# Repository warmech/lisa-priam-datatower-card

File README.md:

# Priam DataTower Interface Card for the Apple Lisa Expansion Bus
 
## Thoughts

If we're going to compile the LOS source code, we're going to need a Priam DataTower. [Said Al Kossow in regard to compiling LOS](https://forum.vcfed.org/index.php?threads/wtb-working-apple-lisa.1246678/page-2):

>you really need something like a Priam Datatower (ie more disk space) to build LOS
>
>the tools are all there in the Version 3 Pascal Workshop.

It seems the compilation process is just too demanding of storage capacity; the 80MB of space the DataTower offered in 1982/3 would have certainly been more than enough (and had a price tag that reflected such a wealth of space).

The driver for the Priam DataTower is baked into LOS and, from the sound of it, no additional software is needed to mount DataTower volumes. Additionally, in the 09/1984 issue of Signal 16, the writers had the following to say regarding the DataTower:

>Signal 16, September 1984
>Priam's DataTower Arrives
>
>Not long after our Signal #13 story about Priam Whamos was published, we got a call from Bill North at Priam, who asked if we would like to find out more about their 86MB disk for the Lisa. The unit is called a DataTower, features a built-in 1/4" tape drive for backup, and is being retailed to the Lisa market as the MassFile by Tecmar. Negotiations began, and phone calls and letters started to wander back and forth between Priam and Semaphore.
>
>Last week, three boxes totaling 110 pounds arrived from San Jose. It was the DataTower. We hate to open a delivery until we're ready to write about it (or at least take good notes), otherwise we might forget some of those interesting first impressions. And, while this copy of Signal was still going through rework at the time (and could easily handle a few last minute changes), we couldn't possibly finish a comprehensive review of the DataTower and include it in the issue. So there was obviously no reason to open the shipment just yet. On the other hand, not opening a newly arrived product is like putting off opening Christmas packages even though it's December 25th. It didn't take long before we reached a compromise: we'd open the shipment, spend just half a day or so checking it out, report on just that much, and then do the rest of the investigation (or at least enough to look like we're making progress) when the next issue rolls around.
>
>We opened the first of the two small boxes and found a blank 1/4" tape cartridge, a power cord, a head cleaning kit, and a photocopy of a 180-page preliminary product specification (slightly too thick for its single staple). The second small box held another blank cartridge, an interface card designed to plug into a Lisa, and a cable to connect the card to the DataTower. The third box held the DataTower itself, contained in a 7" wide, 26" tall and 20" deep metal cabinet that's just right for standing alongside a desk. Unpacking dropped the unit's weight down to about 80 pounds.
>
>It only took us about ten minutes to install everything. The product specification that was included is really engineering documentation designed for programmer types who need to worry about interfacing and writing drivers and all of those esoteric subjects. It doesn't really try to be end user documentation describing how to simply make the unit operate with a Lisa. So we just got out our old Apple documentation on installing a Lisa two-port card, followed all the pictures and went through all the installation steps (but with the Priam card), attached the cable, and powered everything on.
>
>The Lisa we used was an original model that was upgraded to a 2/5, but which still has old ROMs so that the Startup Menu shows two twiggy slots. With the Priam's interface card installed, we were expecting to now find another printed circuit board icon in the Startup Menu. Instead, the menu included an actual little DataTower icon! Those ROMs aren't so old, after all...
>
>We quickly installed a 3.0 Office System on the new disk, and we were off and running. Now Attributes shows 142,420 blocks for our disk device.
>
>One way to think of the DataTower is as something like another Profile, except that it's a lot bigger and faster. Unfortunately, it's noisier too, just enough noisier to be a bit too loud for a nice, calm office environment. Naturally, it's also more expensive. At $8,995 suggested retail, the cost per megabyte is a lot less than on a Profile (and you get the built-in tape drive, too).
>
>Backing up the DataTower is a lot simpler than backing up a Profile, at least in the sense of not requiring a couple of boxes of floppies and lots of operator attention. By duplicating the disk icon, you can start copying the disk to the cartridge tape. So far, we've tried this once and soon realized that 3.0 copies the entire disk image to tape, regardless of how many files are actually stored on the disk, so we canceled the operation once it asked us to insert tape cartridge number two. We'll try a complete save again when we have a bit more time, and let you know how it goes.
>
>We've also started work on an interesting little project that will try to fully exercise the DataTower in a special way. Stay tuned for more details.

This would seem to indicate that the Lisa is capable of booting from a DataTower and that such a boot option will show up at the main boot menu.

The SMART-T protocol documentation is located in the src\priam-src-data directory; this will need to be cross-referenced with the Lisa source code in order to determine next steps for an emulator.

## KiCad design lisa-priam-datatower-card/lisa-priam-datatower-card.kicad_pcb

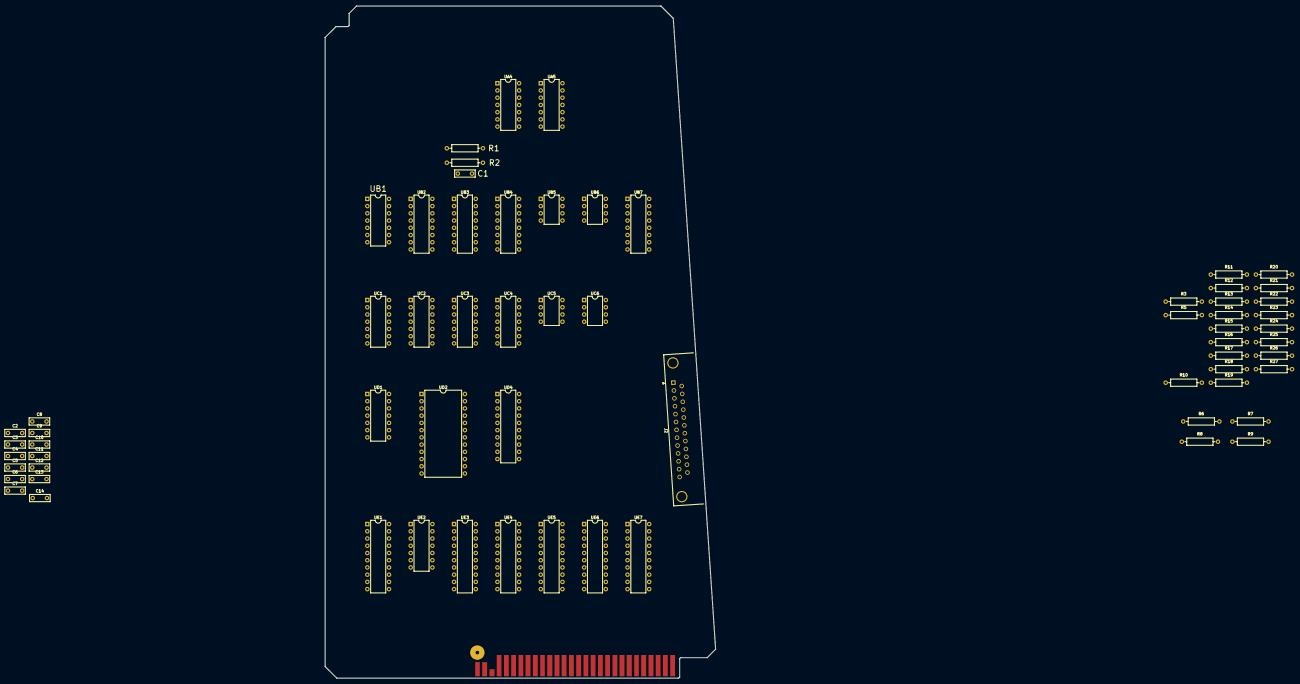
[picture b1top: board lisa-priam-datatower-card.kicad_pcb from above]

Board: 2 copper layers, 137.2 x 236.2 mm, 67 parts (0 on the bottom side), 119 nets, no tracks yet.

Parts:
C1, C2, C3, C4, C5, C6, C7, C8, C9, C10, C11, C12, C13, C14: 0.1uF 50V; C_Disc_D7.0mm_W2.3mm_P5.00mm
J1: Lisa Expansion Card Edge; Apple_Lisa_ExpansionBus_CardEdge
J2: DB25_Receptacle_MountingHoles; DSUB-25_Female_Horizontal_P2.77x2.84mm_EdgePinOffset4.94mm_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
R1, R2, R3, R5: 3.3K; R_Axial_DIN0309_L9.0mm_D2.54mm_P12.70mm_Horizontal
R6, R10, R12, R14, R16, R22, R24, R26: 390; R_Axial_DIN0309_L9.0mm_D2.54mm_P12.70mm_Horizontal
R7, R8, R11, R13, R15, R17, R18, R20, R23, R25, R27: 330; R_Axial_DIN0309_L9.0mm_D2.54mm_P12.70mm_Horizontal
R9, R19, R21: 220; R_Axial_DIN0309_L9.0mm_D2.54mm_P12.70mm_Horizontal
UA4: 74LS164; DIP-14_W7.62mm
UA5: 74LS02; DIP-14_W7.62mm
UB1: 74LS02; DIP-14_W7.62mm
UB2, UB3, UB4, UB7: 74LS112; DIP-16_W7.62mm
UB5, UB6: 75463; DIP-8_W7.62mm
UC1: 74LS125; DIP-14_W7.62mm
UC2: 74LS32; DIP-14_W7.62mm
UC3: 74LS132; DIP-14_W7.62mm
UC4: 74LS00; DIP-14_W7.62mm
UC5, UC6: 75463; DIP-8_W7.62mm
UD1: 74LS00; DIP-14_W7.62mm
UD2: 2716; DIP-24_W15.24mm
UD4: 8304; DIP-20_W7.62mm
UE1, UE4, UE5, UE6, UE7: 74LS374; DIP-20_W7.62mm
UE2: 74LS280; DIP-14_W7.62mm
UE3: 74LS244; DIP-20_W7.62mm

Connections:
+5V: C1.2, C2.2, C3.2, C4.2, C5.2, C6.2, C7.2, C8.2, C9.2, C10.2, C11.2, C12.2, C13.2, C14.2, J1.55 (+5V), J1.56 (+5V), R1.1, R2.1, R3.2, R5.1, R7.2, R9.1, R11.2, R13.2, R15.2, R17.2, R19.2, R21.1, R23.2, R25.2, R27.2, UA4.14 (VCC), UA5.14 (VCC), UB1.14 (VCC), UB2.16 (VCC), UB3.16 (VCC), UB4.16 (VCC), UB5.8 (VCC), UB6.8 (VCC), UB7.16 (VCC), UC1.14 (VCC), UC2.14 (VCC), UC3.14 (VCC), UC4.14 (VCC), UC5.8 (VCC), UC6.8 (VCC), UD1.14 (VCC), UD2.21 (VPP), UD2.24 (VCC), UD4.20 (VCC), UE1.20 (VCC), UE2.14 (VCC), UE3.20 (VCC), UE4.20 (VCC), UE5.20 (VCC), UE6.20 (VCC), UE7.20 (VCC)
/BA1: J1.31 (BA1), UD2.8 (A0), UE1.3 (D0)
/BA2: J1.32 (BA2), UD2.7 (A1), UE1.4 (D1)
/BA3: J1.33 (BA3), UD2.6 (A2), UE1.7 (D2)
/BA4: J1.34 (BA4), UD2.5 (A3), UE1.8 (D3)
/BA5: J1.35 (BA5), UD2.4 (A4), UE1.13 (D4)
/BA7: J1.37 (BA7), UD2.2 (A6), UE1.17 (D6)
/BA8: J1.38 (BA8), UD2.1 (A7), UE1.18 (D7)
/BAA: J1.40 (BA10), UD2.22 (A9)
/BAB: J1.41 (BA11), UD2.19 (A10)
/BD0: J1.30 (BD0), UE3.18 (O0a), UE4.3 (D0), UE5.2 (O0)
/BD1: J1.29 (BD1), UE3.16 (O1a), UE4.4 (D1), UE5.5 (O1)
/BD2: J1.28 (BD2), UE3.14 (O2a), UE4.7 (D2), UE5.6 (O2)
/BD3: J1.27 (BD3), UE3.12 (O3a), UE4.8 (D3), UE5.9 (O3)
/BD4: J1.26 (BD4), UE3.9 (O0b), UE4.13 (D4), UE5.12 (O4)
/BD5: J1.25 (BD5), UE3.7 (O1b), UE4.14 (D5), UE5.15 (O5)
/BD6: J1.24 (BD6), UE3.5 (O2b), UE4.17 (D6), UE5.16 (O6)
/BD7: J1.23 (BD7), UE3.3 (O3b), UE4.18 (D7), UE5.19 (O7)
/BD8: J1.22 (BD8), UE6.3 (D0), UE7.2 (O0)
/BD9: J1.21 (BD9), UE6.4 (D1), UE7.5 (O1)
/BDA: J1.20 (BD10), UE6.7 (D2), UE7.6 (O2)
/BDB: J1.19 (BD11), UE6.8 (D3), UE7.9 (O3)
/BDC: J1.18 (BD12), UE6.13 (D4), UE7.12 (O4)
/BDD: J1.17 (BD13), UE6.14 (D5), UE7.15 (O5)
/BDE: J1.16 (BD14), UE6.17 (D6), UE7.16 (O6)
/BDF: J1.15 (BD15), UC1.3, UE6.18 (D7), UE7.19 (O7)
/LD0: UD4.1 (A0), UE2.8 (A), UE4.2 (O0), UE5.3 (D0), UE6.2 (O0), UE7.3 (D0)
/LD1: UD4.2 (A1), UE2.9 (B), UE4.5 (O1), UE5.4 (D1), UE6.5 (O1), UE7.4 (D1)
/LD2: UD4.3 (A2), UE2.10 (C), UE4.6 (O2), UE5.7 (D2), UE6.6 (O2), UE7.7 (D2)
/LD3: UD4.4 (A3), UE2.11 (D), UE4.9 (O3), UE5.8 (D3), UE6.9 (O3), UE7.8 (D3)
/LD4: UD4.5 (A4), UE2.12 (E), UE4.12 (O4), UE5.13 (D4), UE6.12 (O4), UE7.13 (D4)
/LD5: UD4.6 (A5), UE2.13 (F), UE4.15 (O5), UE5.14 (D5), UE6.15 (O5), UE7.14 (D5)
/LD6: UD4.7 (A6), UE2.1 (G), UE4.16 (O6), UE5.17 (D6), UE6.16 (O6), UE7.17 (D6)
/LD7: UD4.8 (A7), UE2.2 (H), UE4.19 (O7), UE5.18 (D7), UE6.19 (O7), UE7.18 (D7)
BA6: J1.36 (BA6), UB1.5, UB1.6, UD2.3 (A5), UE1.14 (D5)
BA9: J1.39 (BA9), UC2.12, UD2.23 (A8)
CKH: UC4.8, UE7.11 (Cp)
CKL: UC4.11, UE5.11 (Cp)
CKP: UB3.5 (Q), UB4.1 (C), UC4.10, UC4.12
CPUCK: J1.8 (CPUCK), UB3.13 (C), UB7.1 (C), UB7.13 (C)
GND: C1.1, C2.1, C3.1, C4.1, C5.1, C6.1, C7.1, C8.1, C9.1, C10.1, C11.1, C12.1, C13.1, C14.1, J1.53 (GND), J1.54 (GND), J2.0 (PAD), J2.1, J2.2, J2.4, J2.9, J2.20, J2.24, R6.1, R8.2, R10.1, R12.1, R14.1, R16.1, R18.2, R20.2, R22.1, R24.1, R26.1, UA4.7 (GND), UA5.7 (GND), UB1.7 (GND), UB2.8 (GND), UB3.8 (GND), UB4.2 (K), UB4.8 (GND), UB4.11 (J), UB5.4 (GND), UB6.4 (GND), UB7.8 (GND), UC1.5, UC1.7 (GND), UC2.7 (GND), UC3.7 (GND), UC4.7 (GND), UC5.4 (GND), UC6.4 (GND), UD1.7 (GND), UD2.12 (GND), UD2.18 (/CE), UD2.20 (/OE), UD4.10 (GND), UE1.1 (OE), UE1.10 (GND), UE2.7 (GND), UE3.10 (GND), UE4.10 (GND), UE5.10 (GND), UE6.10 (GND), UE7.10 (GND)
HAD0: J2.16, UB5.5
HAD1: J2.17, UB5.3
HAD2: J2.19, UB6.5
HCBUS0: J2.5, R6.2, R7.1, UD4.19 (B0)
HCBUS1: J2.6, R10.2, R11.1, UD4.18 (B1)
HCBUS2: J2.8, R12.2, R13.1, UD4.17 (B2)
HCBUS3: J2.22, R14.2, R15.1, UD4.16 (B3)
HCBUS4: J2.23, R16.2, R17.1, UD4.15 (B4)
HCBUS5: J2.11, R22.2, R23.1, UD4.14 (B5)
HCBUS6: J2.12, R24.2, R25.1, UD4.13 (B6)
HCBUS7: J2.13, R26.2, R27.1, UD4.12 (B7)
HCBUSP: J2.18, R8.1, R9.2, UC3.1, UC5.3
HUNK: J2.14, UB6.3
LA1: UB5.6, UE1.2 (O0)
LA2: UB5.2, UE1.5 (O1)
LA3: UB6.6, UE1.6 (O2)
LA4: UB6.2, UE1.9 (O3)
LA5: UB4.15 (~R), UE1.12 (O4)
LA7: UD1.13, UE1.16 (O6)
LA8: UC3.9, UE1.19 (O7)
unnamed: J1.13 (/BGINn), J1.14 (/BGOUTn)
unnamed: J1.6 (/IAKn), J1.44 (/VPA)
unnamed: UA4.1 (A), UA4.2 (B), UB2.5 (Q), UC4.1, UC4.9
unnamed: UA4.8 (CLK), UB2.1 (C), UB2.13 (C), UB4.13 (C), UB7.9 (Q)
unnamed: UA4.4 (Qb), UA5.2, UB2.11 (J)
unnamed: UA4.5 (Qc), UA5.3
unnamed: UB1.1, UC1.9
unnamed: UB1.3, UB1.4
unnamed: UA5.1, UB2.3 (J)
unnamed: UB2.6 (~Q), UD1.10
unnamed: UB1.2, UB2.9 (Q), UB4.12 (K), UC4.5, UC4.13, UD1.12
unnamed: UB2.7 (~Q), UD1.9
unnamed: UB1.8, UB3.1 (C), UB7.6 (~Q)
unnamed: UB3.2 (K), UB3.3 (J), UD1.8
unnamed: UB3.6 (~Q), UC6.1, UC6.7
unnamed: UB3.15 (~R), UD1.11
unnamed: UB3.9 (Q), UB7.2 (K), UB7.3 (J)
unnamed: UB1.9, UB3.7 (~Q)
unnamed: UB4.5 (Q), UC1.2
unnamed: R3.1, UB4.4 (~S)
unnamed: UB4.10 (~S), UC2.11
unnamed: UB1.10, UB7.11 (J), UB7.12 (K)
unnamed: UC2.5, UC2.10, UC3.6
unnamed: UC3.2, UC5.1, UC6.6, UD1.3, UD1.4
unnamed: UC3.10, UC3.11
unnamed: UD2.9 (D0), UE3.2 (I0a)
unnamed: UD2.10 (D1), UE3.4 (I1a)
unnamed: UD2.11 (D2), UE3.6 (I2a)
unnamed: UD2.13 (D3), UE3.8 (I3a)
unnamed: UD2.14 (D4), UE3.11 (I0b)
unnamed: UD2.15 (D5), UE3.13 (I1b)
unnamed: UD2.16 (D6), UE3.15 (I2b)
unnamed: UD2.17 (D7), UE3.17 (I3b)
PIN: UC3.3, UE2.4 (I)
POUT: UB4.3 (J), UC5.2, UE2.5 (Even)
PU1: R1.2, UB3.11 (J), UB3.12 (K), UB3.14 (~R)
PU2: R2.2, UB3.4 (~S)
PU5: R5.2, UB2.2 (K), UB2.4 (~S), UB2.10 (~S), UB2.12 (K), UB7.4 (~S), UB7.10 (~S)
READ: J1.48 (READ), UC2.2, UC3.4, UC3.5
SHI: UB1.13, UE1.11 (Cp), UE4.11 (Cp), UE6.11 (Cp)
WR: UC4.2, UC4.4, UC6.2, UD1.2, UD1.6, UD4.11 (T/R)
/BTREQ: J2.10, R20.1, R21.2, UC3.12
/BUSE: UB4.7 (~Q), UB5.1, UB5.7, UB6.1, UB6.7, UD4.9 (CD)
/DTACK: J1.46 (/DTACK), UC1.6, UC1.8
/FFR: UA4.9 (/CLR), UB2.14 (~R), UB2.15 (~R), UB4.9 (Q), UB7.14 (~R), UB7.15 (~R), UD1.1
/HIR: J2.25, R18.1, R19.1, UC3.13
/HIRD: UC2.8, UE5.1 (OE), UE7.1 (OE)
/HIWR: UC2.3, UD1.5
/HRD: J2.15, UC6.3
/HRST: J2.21, UC5.5
/HWR: J2.3, UC6.5
/INTn: J1.5 (/INTn), UC3.8
/LORD: UC1.1, UC2.6, UE3.1 (OEa), UE3.19 (OEb)
/OEH: UC4.3, UE6.1 (OE)
/OEL: UC4.6, UE4.1 (OE)
/RESET: J1.7 (/RESET), UB4.14 (~R), UC5.6, UC5.7
/SH: UB1.11, UB1.12, UC1.10, UC2.1, UC2.9, UC2.13
/SL: UC1.4, UC2.4

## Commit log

2024-02-23 updates - pcb created
2024-02-28 rev 1.0 complete
2024-03-01 final update for now...
2024-04-09 Correction: LA6 changed to LAA on LS374
